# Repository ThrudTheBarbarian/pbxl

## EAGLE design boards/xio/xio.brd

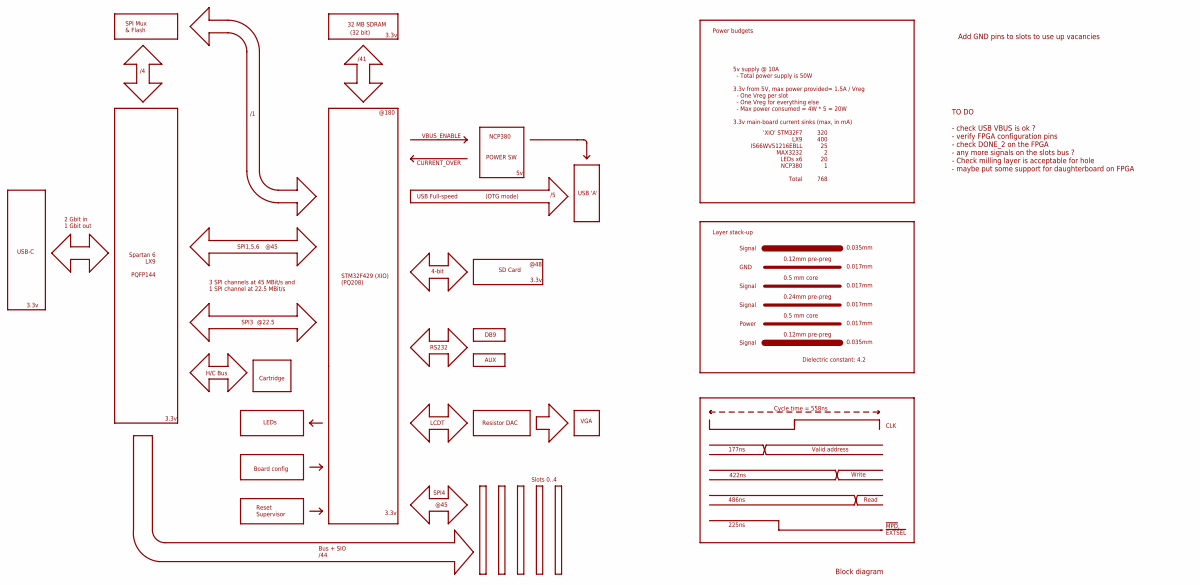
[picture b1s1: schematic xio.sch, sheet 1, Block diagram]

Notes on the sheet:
USB-C
3.3v
STM32F429 (XIO) (PQ208)
SPI4
@45
Slots 0..4
Bus + SIO /44
RS232
32 MB SDRAM
/41
(32 bit)
POWER SW
USB Full-speed
CURRENT_OVER
VBUS_ENABLE
SD Card
@48
@180
NCP380
(OTG mode)
USB 'A'
DB9
5v supply @ 10A - Total power supply is 50W 3.3v from 5V, max power provided= 1.5A / Vreg - One Vreg per slot - One Vreg for everything else - Max power consumed = 4W * 5 = 20W 3.3v main-board current sinks (max, in mA)
'XIO' STM32F7 LX9 IS66WV51216EBLL MAX3232 LEDs x6 NCP380 Total
320 400 25 2 20 1 768
0.5 mm core
0.12mm pre-preg
0.035mm
0.017mm
Layer stack-up
GND
Power
Dielectric constant: 4.2
Cycle time = 558ns
Valid address
Write
Read
177ns
422ns
486ns

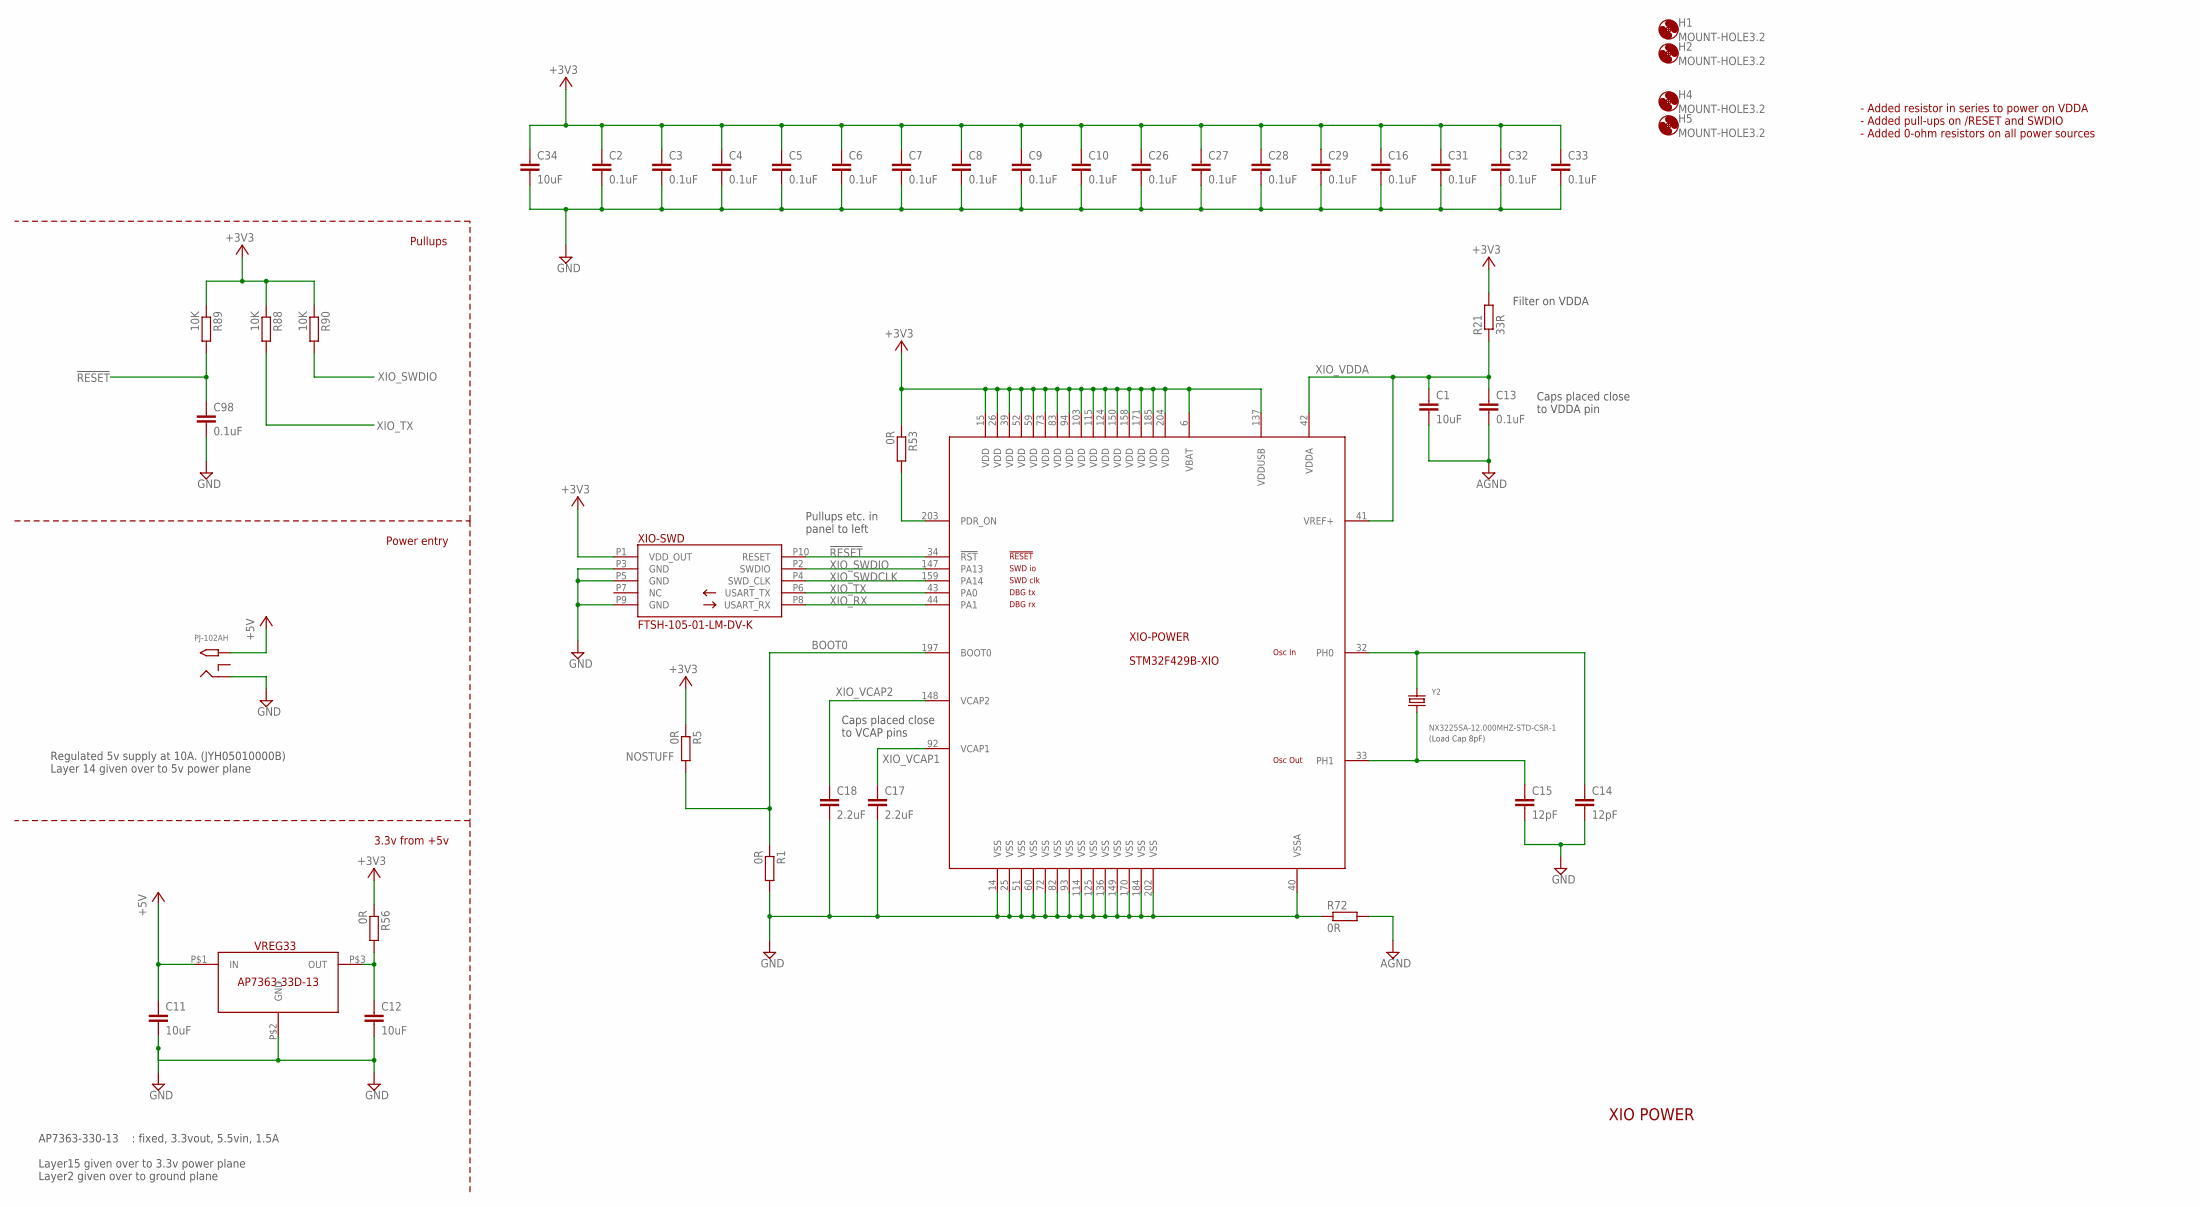
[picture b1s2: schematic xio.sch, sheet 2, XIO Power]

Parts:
C1, C11, C12, C34: 10uF; C0402K
C2, C3, C4, C5, C6, C7, C8, C9, C10, C13, C16, C26, C27, C28, C29, C31, C32, C33, C98: 0.1uF; C0402K
C14, C15: 12pF; C0402K
C17, C18: 2.2uF; C0402K
H1, H2, H4, H5: MOUNT-HOLE3.2; 3,2
PJ-102AH: PJ-102AH; PJ-102A
R1, R5, R53, R56, R72: 0R; R0402
R21: 33R; R0402
R88, R89, R90: 10K; R0402
VREG33: AP7363-33D-13; TO252-3L
XIO: STM32F429B-XIO; PQFP208
XIO-SWD: FTSH-105-01-LM-DV-K; SWD_DEBUG
Y2: NX3225SA-12.000MHZ-STD-CSR-1; CRYSTAL_3.2X2.5

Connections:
!RESET!: C98.1, R89.2, XIO.34 (!RST!), XIO-SWD.P10 (RESET); also elsewhere on the board
+3V3: C2.1, C3.1, C4.1, C5.1, C6.1, C7.1, C8.1, C9.1, C10.1, C16.1, C26.1, C27.1, C28.1, C29.1, C31.1, C32.1, C33.1, C34.1, R5.1, R21.2, R53.1, R56.1, R88.1, R89.1, R90.1, XIO.6 (VBAT), XIO.15 (VDD), XIO.26 (VDD), XIO.39 (VDD), XIO.52 (VDD), XIO.59 (VDD), XIO.73 (VDD), XIO.83 (VDD), XIO.94 (VDD), XIO.103 (VDD), XIO.115 (VDD), XIO.124 (VDD), XIO.137 (VDDUSB), XIO.150 (VDD), XIO.158 (VDD), XIO.171 (VDD), XIO.185 (VDD), XIO.204 (VDD), XIO-SWD.P1 (VDD_OUT); also elsewhere on the board
+5V: C11.1, PJ-102AH.TIP, VREG33.P$1 (IN); also elsewhere on the board
AGND: C1.2, C13.2, R72.2
BOOT0: R1.1, R5.2, XIO.197 (BOOT0)
GND: C2.2, C3.2, C4.2, C5.2, C6.2, C7.2, C8.2, C9.2, C10.2, C11.2, C12.2, C14.2, C15.2, C16.2, C17.2, C18.2, C26.2, C27.2, C28.2, C29.2, C31.2, C32.2, C33.2, C34.2, C98.2, PJ-102AH.RING, R1.2, R72.1, VREG33.P$2 (GND), XIO.14 (VSS), XIO.25 (VSS), XIO.40 (VSSA), XIO.51 (VSS), XIO.60 (VSS), XIO.72 (VSS), XIO.82 (VSS), XIO.93 (VSS), XIO.114 (VSS), XIO.125 (VSS), XIO.136 (VSS), XIO.149 (VSS), XIO.170 (VSS), XIO.184 (VSS), XIO.202 (VSS), XIO-SWD.P3 (GND), XIO-SWD.P5 (GND), XIO-SWD.P9 (GND); also elsewhere on the board
unnamed: C15.1, XIO.33 (PH1), Y2.1
unnamed: C14.1, XIO.32 (PH0), Y2.2
unnamed: C12.1, R56.2, VREG33.P$3 (OUT)
PDR_ON: R53.2, XIO.203 (PDR_ON)
XIO_RX: XIO.44 (PA1), XIO-SWD.P8 (USART_RX)
XIO_SWDCLK: XIO.159 (PA14), XIO-SWD.P4 (SWD_CLK)
XIO_SWDIO: R90.2, XIO.147 (PA13), XIO-SWD.P2 (SWDIO)
XIO_TX: R88.2, XIO.43 (PA0), XIO-SWD.P6 (USART_TX)
XIO_VCAP1: C17.1, XIO.92 (VCAP1)
XIO_VCAP2: C18.1, XIO.148 (VCAP2)
XIO_VDDA: C1.1, C13.1, R21.1, XIO.41 (VREF+), XIO.42 (VDDA)

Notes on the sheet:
Power entry
3.3v from +5v
XIO POWER
AP7363-330-13 : fixed, 3.3vout, 5.5vin, 1.5A Layer15 given over to 3.3v power plane Layer2 given over to ground plane
Regulated 5v supply at 10A. (JYH05010000B) Layer 14 given over to 5v power plane
Caps placed close to VDDA pin
Caps placed close to VCAP pins
(Load Cap 8pF)
Pullups
- Added resistor in series to power on VDDA - Added pull-ups on /RESET and SWDIO - Added 0-ohm resistors on all power sources
Filter on VDDA
Pullups etc. in panel to left

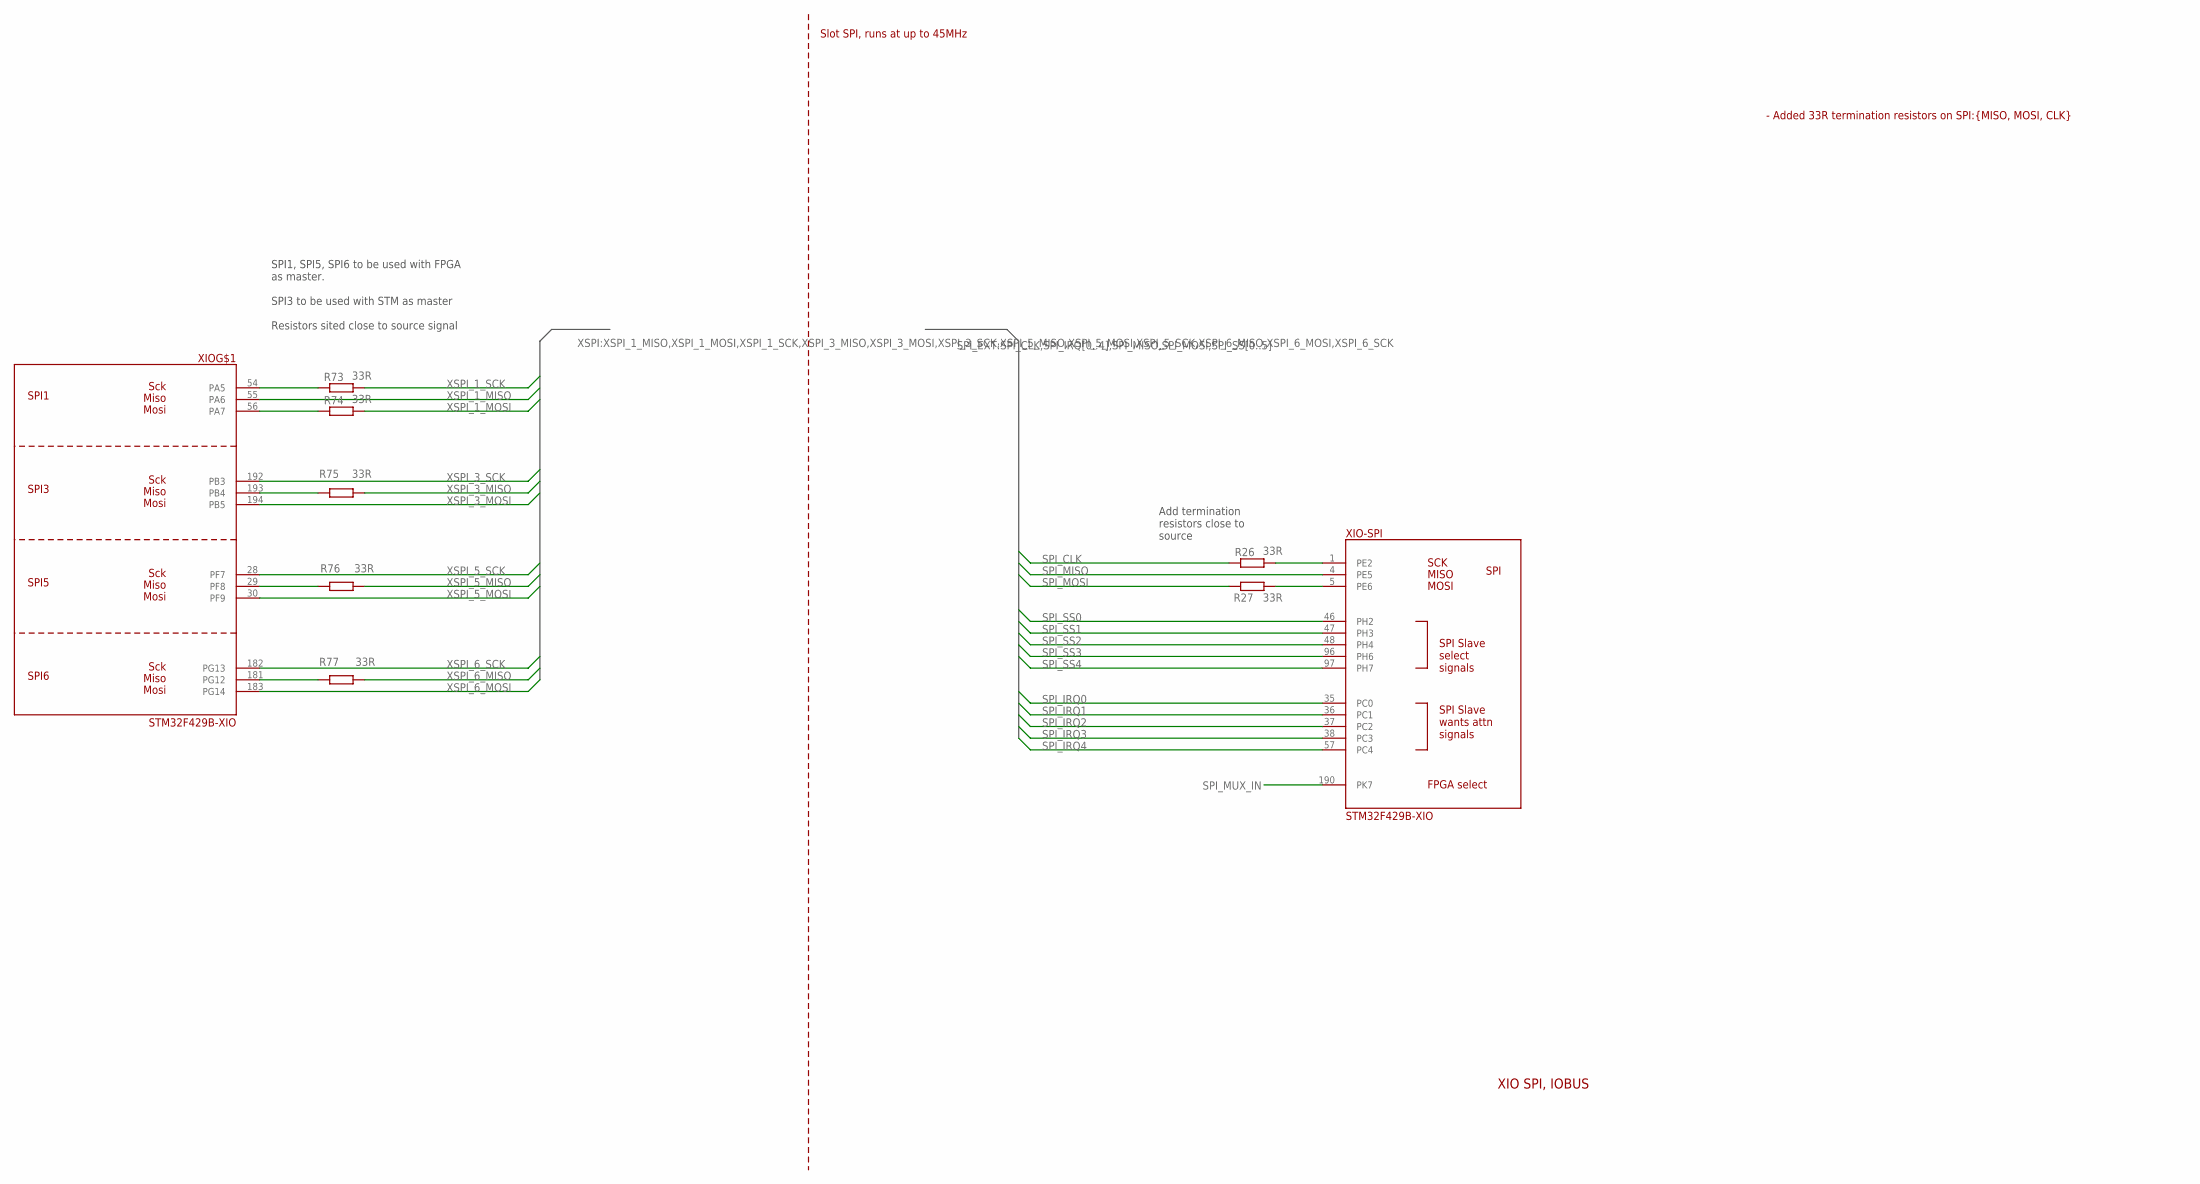
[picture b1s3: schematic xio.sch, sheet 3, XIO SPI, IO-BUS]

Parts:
R26, R27, R73, R74, R75, R76, R77: 33R; R0402
XIO: STM32F429B-XIO; PQFP208

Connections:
unnamed: R26.2, XIO.1 (PE2)
unnamed: R27.2, XIO.5 (PE6)
unnamed: R75.1, XIO.193 (PB4)
unnamed: R76.1, XIO.29 (PF8)
unnamed: R77.1, XIO.181 (PG12)
unnamed: R73.1, XIO.54 (PA5)
unnamed: R74.1, XIO.56 (PA7)
SPI_CLK: R26.1; also elsewhere on the board
SPI_IRQ0: XIO.35 (PC0); also elsewhere on the board
SPI_IRQ1: XIO.36 (PC1); also elsewhere on the board
SPI_IRQ2: XIO.37 (PC2); also elsewhere on the board
SPI_IRQ3: XIO.38 (PC3); also elsewhere on the board
SPI_IRQ4: XIO.57 (PC4); also elsewhere on the board
SPI_MISO: XIO.4 (PE5); also elsewhere on the board
SPI_MOSI: R27.1; also elsewhere on the board
SPI_MUX_IN: XIO.190 (PK7); also elsewhere on the board
SPI_SS0: XIO.46 (PH2); also elsewhere on the board
SPI_SS1: XIO.47 (PH3); also elsewhere on the board
SPI_SS2: XIO.48 (PH4); also elsewhere on the board
SPI_SS3: XIO.96 (PH6); also elsewhere on the board
SPI_SS4: XIO.97 (PH7); also elsewhere on the board
XSPI_1_MISO: XIO.55 (PA6); also elsewhere on the board
XSPI_1_MOSI: R74.2; also elsewhere on the board
XSPI_1_SCK: R73.2; also elsewhere on the board
XSPI_3_MISO: R75.2; also elsewhere on the board
XSPI_3_MOSI: XIO.194 (PB5); also elsewhere on the board
XSPI_3_SCK: XIO.192 (PB3); also elsewhere on the board
XSPI_5_MISO: R76.2; also elsewhere on the board
XSPI_5_MOSI: XIO.30 (PF9); also elsewhere on the board
XSPI_5_SCK: XIO.28 (PF7); also elsewhere on the board
XSPI_6_MISO: R77.2; also elsewhere on the board
XSPI_6_MOSI: XIO.183 (PG14); also elsewhere on the board
XSPI_6_SCK: XIO.182 (PG13); also elsewhere on the board

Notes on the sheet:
Slot SPI, runs at up to 45MHz
XIO SPI, IOBUS
Add termination resistors close to source
- Added 33R termination resistors on SPI:{MISO, MOSI, CLK}
SPI1, SPI5, SPI6 to be used with FPGA as master. SPI3 to be used with STM as master Resistors sited close to source signal

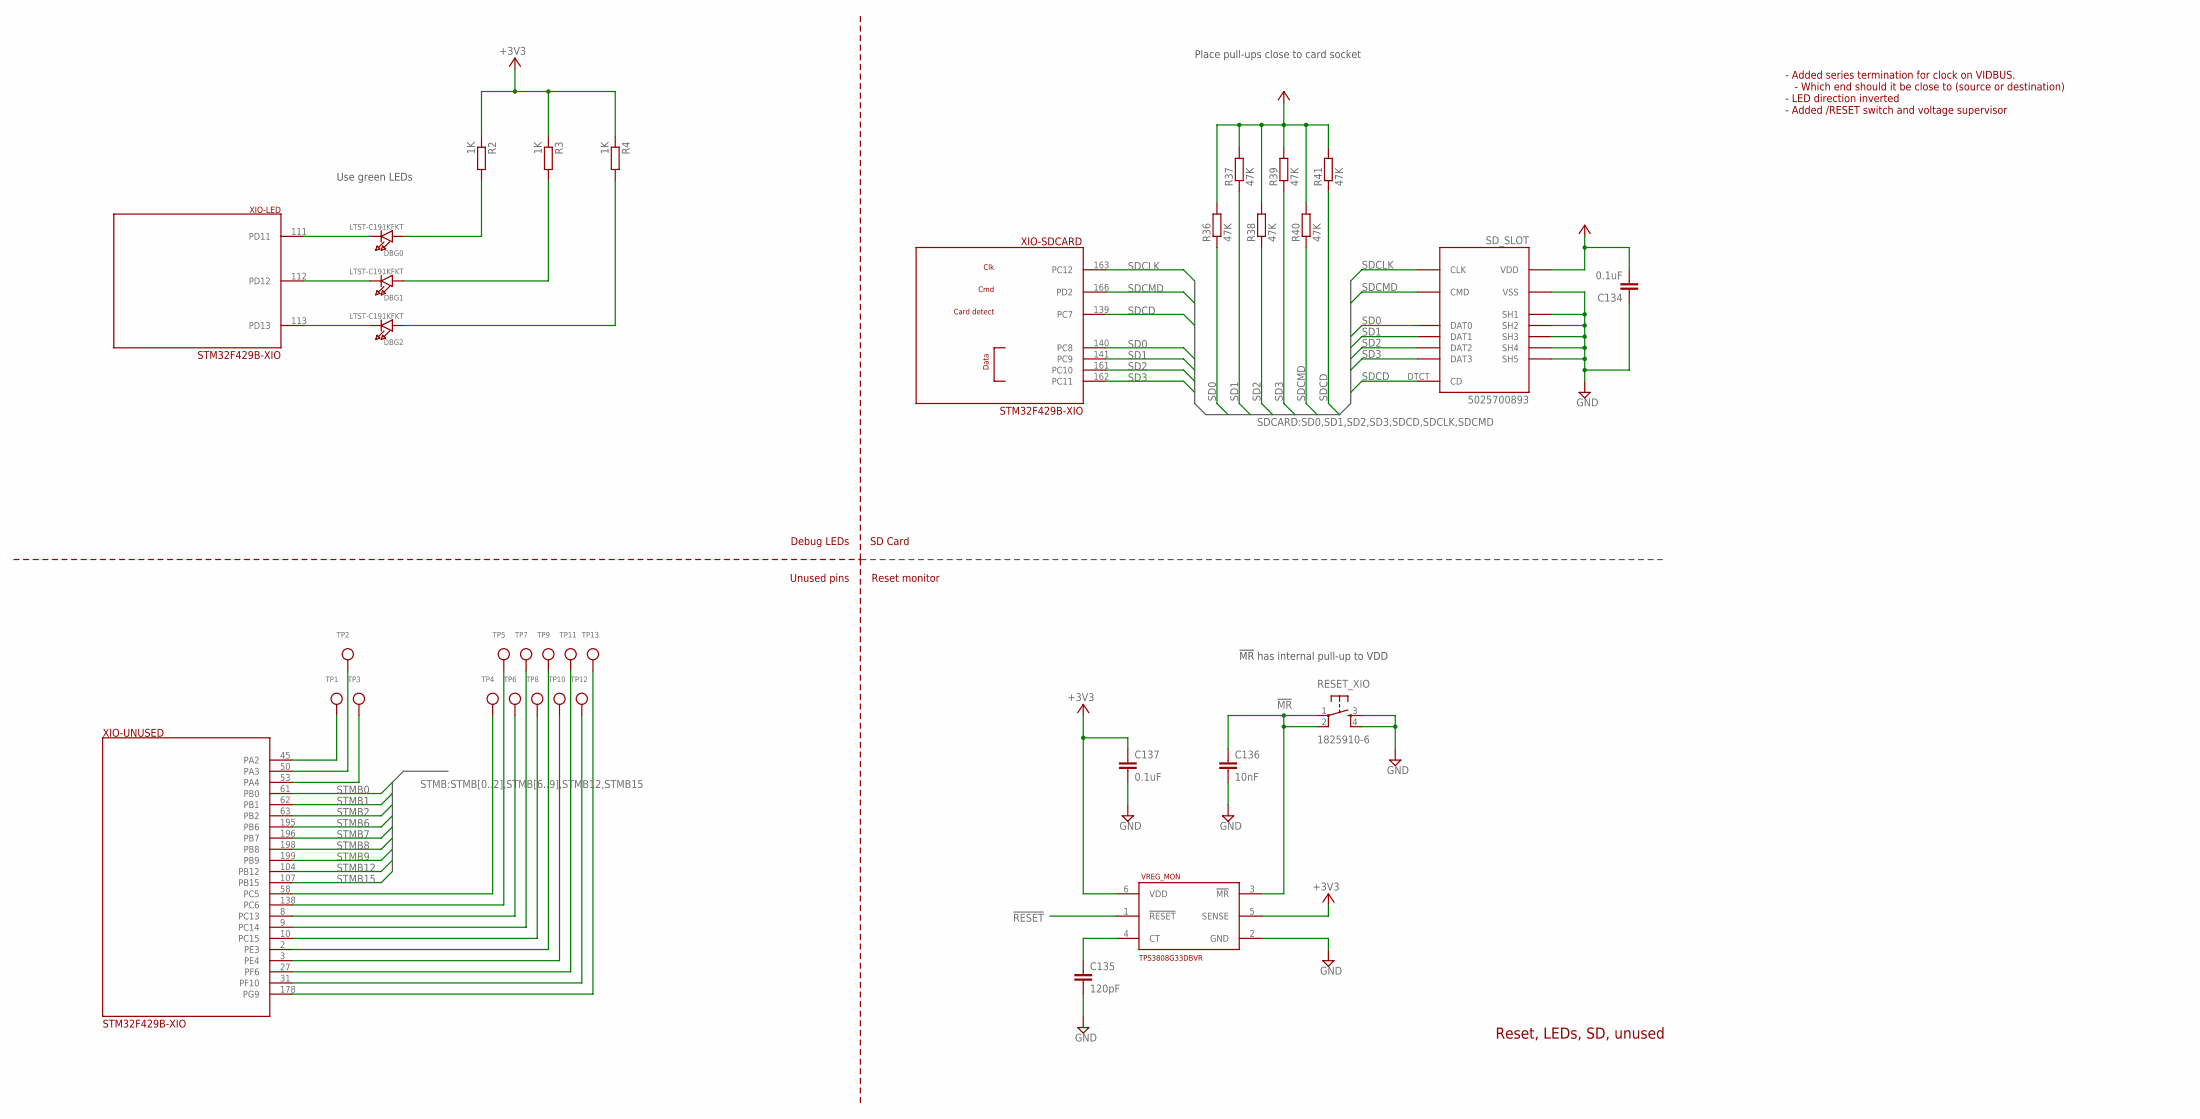
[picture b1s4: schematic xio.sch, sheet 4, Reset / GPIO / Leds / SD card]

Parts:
C134, C137: 0.1uF; C0402K
C135: 120pF; C0402K
C136: 10nF; C0402K
DBG0, DBG1, DBG2: LTST-C191KFKT; CHIPLED_0603
R2, R3, R4: 1K; R0402
R36, R37, R38, R39, R40, R41: 47K; R0402
RESET_XIO: 1825910-6; TACTILE-PTH
SD_SLOT: 5025700893
TP1, TP2, TP3, TP4, TP5, TP6, TP7, TP8, TP9, TP10, TP11, TP12, TP13: TESTPOINTROUND0.5MM; TESTPOINT_ROUND_0.5MM
VREG_MON: TPS3808G33DBVR; SOT23-6
XIO: STM32F429B-XIO; PQFP208

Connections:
!MR!: C136.1, RESET_XIO.1, RESET_XIO.2, VREG_MON.3 (!MR!)
!RESET!: VREG_MON.1 (!RESET!); also elsewhere on the board
+3V3: C134.2, C137.1, R2.1, R3.1, R4.1, R36.2, R37.2, R38.2, R39.2, R40.2, R41.2, SD_SLOT.P$4 (VDD), VREG_MON.5 (SENSE), VREG_MON.6 (VDD); also elsewhere on the board
GND: C134.1, C135.2, C136.2, C137.2, RESET_XIO.3, RESET_XIO.4, SD_SLOT.GND0 (SH1), SD_SLOT.GND1 (SH2), SD_SLOT.GND2 (SH3), SD_SLOT.GND3 (SH4), SD_SLOT.GND4 (SH5), SD_SLOT.P$6 (VSS), VREG_MON.2 (GND); also elsewhere on the board
unnamed: DBG0.A, R2.2
unnamed: DBG0.C, XIO.111 (PD11)
unnamed: DBG1.C, XIO.112 (PD12)
unnamed: DBG2.C, XIO.113 (PD13)
unnamed: DBG1.A, R3.2
unnamed: DBG2.A, R4.2
unnamed: C135.1, VREG_MON.4 (CT)
unnamed: TP1.P$1, XIO.45 (PA2)
unnamed: TP2.P$1, XIO.50 (PA3)
unnamed: TP3.P$1, XIO.53 (PA4)
unnamed: TP4.P$1, XIO.58 (PC5)
unnamed: TP5.P$1, XIO.138 (PC6)
unnamed: TP6.P$1, XIO.8 (PC13)
unnamed: TP7.P$1, XIO.9 (PC14)
unnamed: TP8.P$1, XIO.10 (PC15)
unnamed: TP9.P$1, XIO.2 (PE3)
unnamed: TP10.P$1, XIO.3 (PE4)
unnamed: TP11.P$1, XIO.27 (PF6)
unnamed: TP12.P$1, XIO.31 (PF10)
unnamed: TP13.P$1, XIO.178 (PG9)
SD0: R36.1, SD_SLOT.P$7 (DAT0), XIO.140 (PC8)
SD1: R37.1, SD_SLOT.P$8 (DAT1), XIO.141 (PC9)
SD2: R38.1, SD_SLOT.P$1 (DAT2), XIO.161 (PC10)
SD3: R39.1, SD_SLOT.P$2 (DAT3), XIO.162 (PC11)
SDCD: R41.1, SD_SLOT.DTCT (CD), XIO.139 (PC7)
SDCLK: SD_SLOT.P$5 (CLK), XIO.163 (PC12)
SDCMD: R40.1, SD_SLOT.P$3 (CMD), XIO.166 (PD2)
STMB0: XIO.61 (PB0); also elsewhere on the board
STMB1: XIO.62 (PB1); also elsewhere on the board
STMB2: XIO.63 (PB2); also elsewhere on the board
STMB6: XIO.195 (PB6); also elsewhere on the board
STMB7: XIO.196 (PB7); also elsewhere on the board
STMB8: XIO.198 (PB8); also elsewhere on the board
STMB9: XIO.199 (PB9); also elsewhere on the board
STMB12: XIO.104 (PB12); also elsewhere on the board
STMB15: XIO.107 (PB15); also elsewhere on the board

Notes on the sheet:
Debug LEDs
Unused pins
Reset, LEDs, SD, unused
Use green LEDs
Reset monitor
!MR! has internal pull-up to VDD
- Added series termination for clock on VIDBUS. - Which end should it be close to (source or destination) - LED direction inverted - Added /RESET switch and voltage supervisor
SD Card
Place pull-ups close to card socket

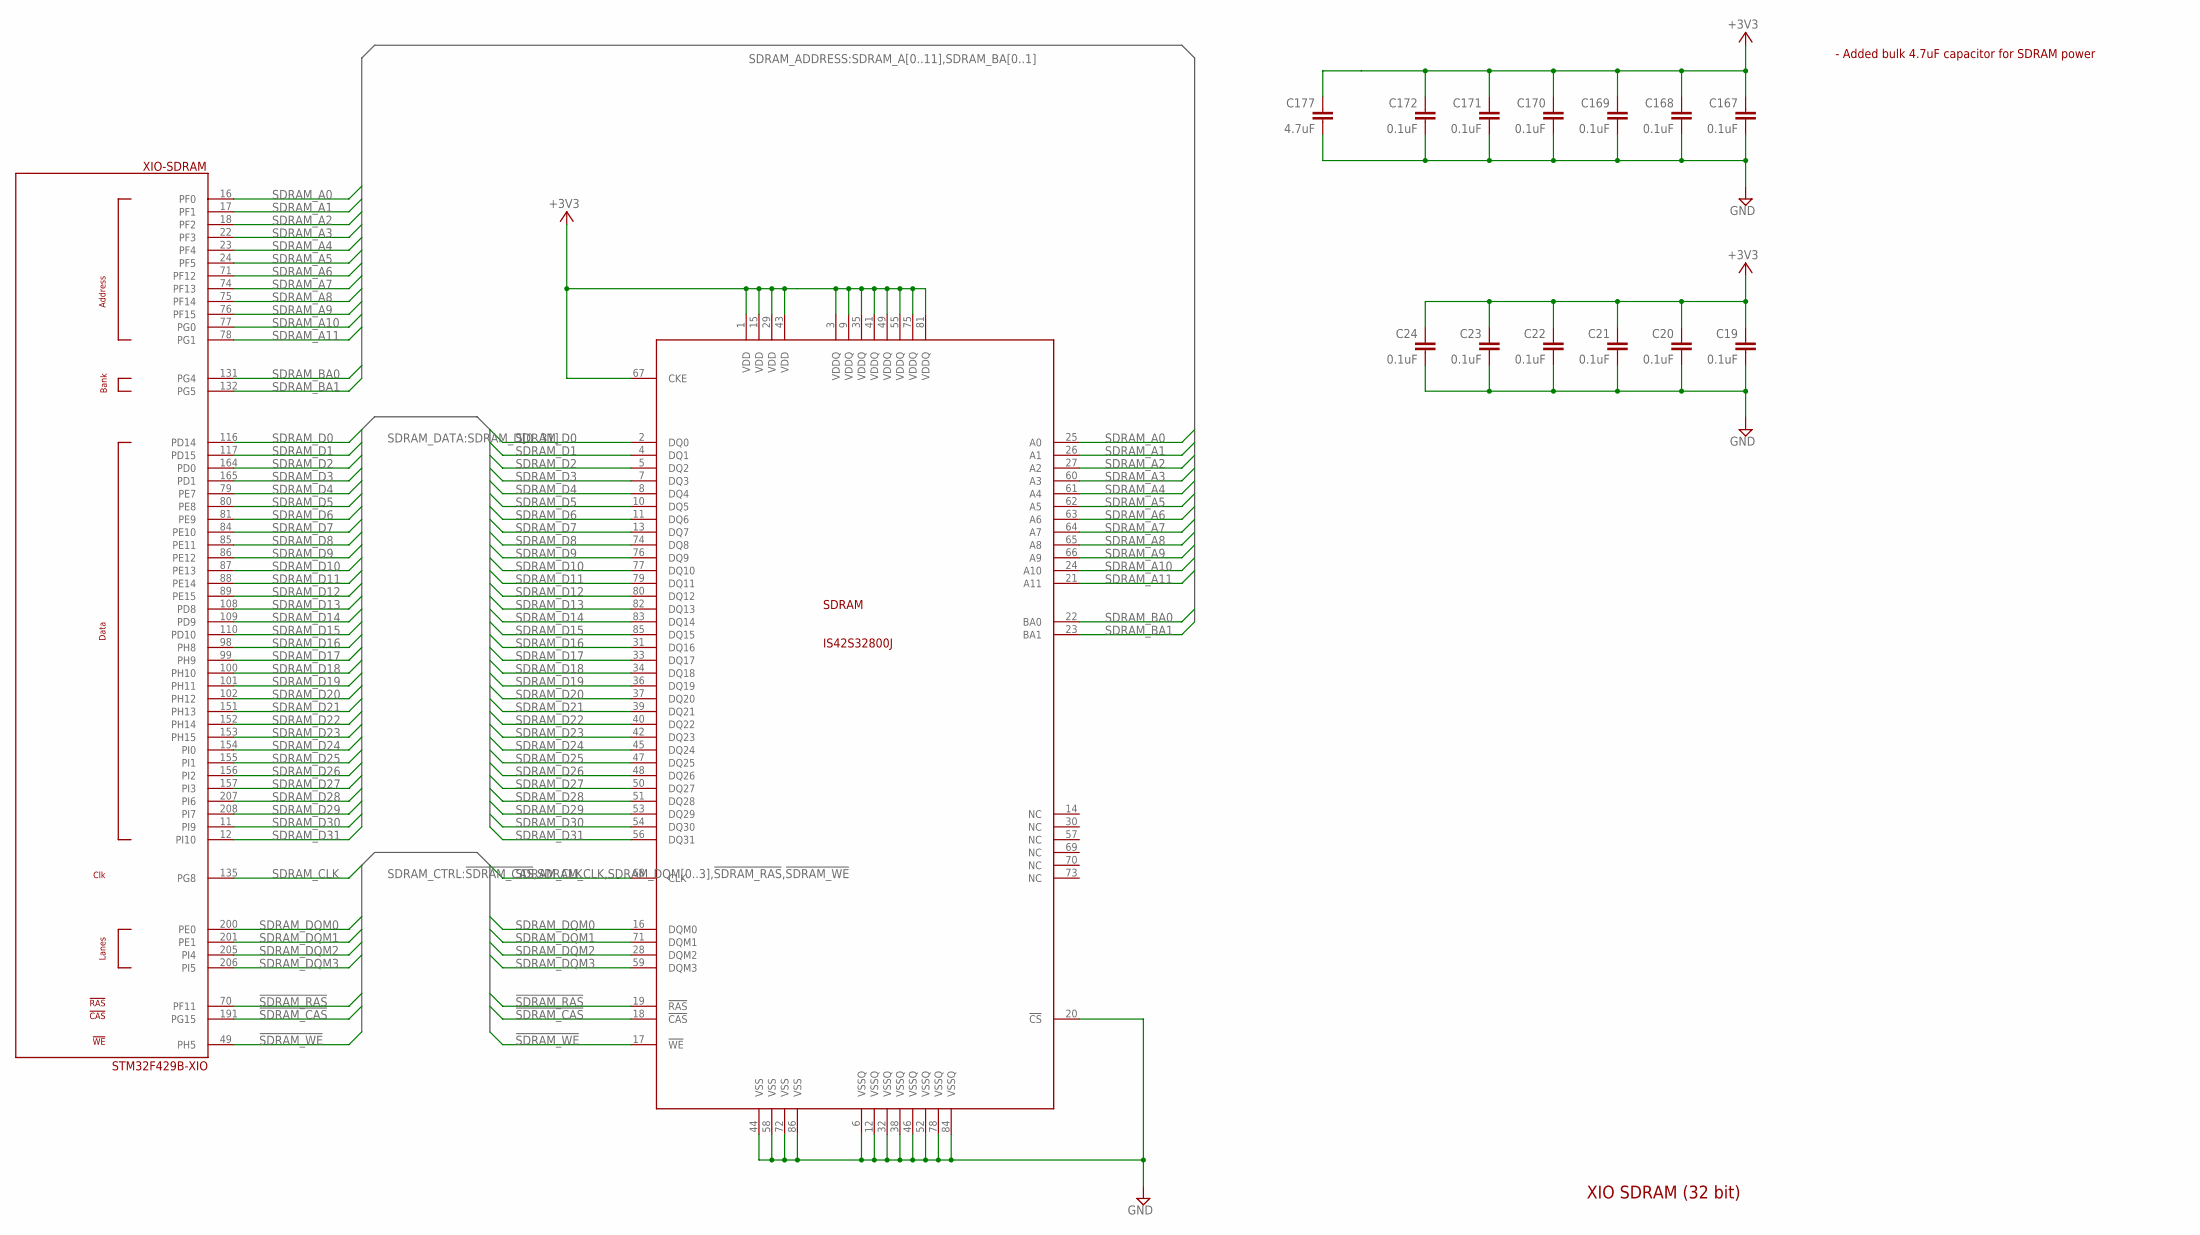
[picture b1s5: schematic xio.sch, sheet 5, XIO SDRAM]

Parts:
C19, C20, C21, C22, C23, C24, C167, C168, C169, C170, C171, C172: 0.1uF; C0402K
C177: 4.7uF; C0402K
SDRAM: IS42S32800J; SOP50P1176X120-86
XIO: STM32F429B-XIO; PQFP208

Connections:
!SDRAM_CAS!: SDRAM.18 (!CAS!), XIO.191 (PG15)
!SDRAM_RAS!: SDRAM.19 (!RAS!), XIO.70 (PF11)
!SDRAM_WE!: SDRAM.17 (!WE!), XIO.49 (PH5)
+3V3: C19.1, C20.1, C21.1, C22.1, C23.1, C24.1, C167.1, C168.1, C169.1, C170.1, C171.1, C172.1, C177.1, SDRAM.1 (VDD), SDRAM.3 (VDDQ), SDRAM.9 (VDDQ), SDRAM.15 (VDD), SDRAM.29 (VDD), SDRAM.35 (VDDQ), SDRAM.41 (VDDQ), SDRAM.43 (VDD), SDRAM.49 (VDDQ), SDRAM.55 (VDDQ), SDRAM.67 (CKE), SDRAM.75 (VDDQ), SDRAM.81 (VDDQ); also elsewhere on the board
GND: C19.2, C20.2, C21.2, C22.2, C23.2, C24.2, C167.2, C168.2, C169.2, C170.2, C171.2, C172.2, C177.2, SDRAM.6 (VSSQ), SDRAM.12 (VSSQ), SDRAM.20 (!CS!), SDRAM.32 (VSSQ), SDRAM.38 (VSSQ), SDRAM.44 (VSS), SDRAM.46 (VSSQ), SDRAM.52 (VSSQ), SDRAM.58 (VSS), SDRAM.72 (VSS), SDRAM.78 (VSSQ), SDRAM.84 (VSSQ), SDRAM.86 (VSS); also elsewhere on the board
SDRAM_A0: SDRAM.25 (A0), XIO.16 (PF0)
SDRAM_A1: SDRAM.26 (A1), XIO.17 (PF1)
SDRAM_A2: SDRAM.27 (A2), XIO.18 (PF2)
SDRAM_A3: SDRAM.60 (A3), XIO.22 (PF3)
SDRAM_A4: SDRAM.61 (A4), XIO.23 (PF4)
SDRAM_A5: SDRAM.62 (A5), XIO.24 (PF5)
SDRAM_A6: SDRAM.63 (A6), XIO.71 (PF12)
SDRAM_A7: SDRAM.64 (A7), XIO.74 (PF13)
SDRAM_A8: SDRAM.65 (A8), XIO.75 (PF14)
SDRAM_A9: SDRAM.66 (A9), XIO.76 (PF15)
SDRAM_A10: SDRAM.24 (A10), XIO.77 (PG0)
SDRAM_A11: SDRAM.21 (A11), XIO.78 (PG1)
SDRAM_BA0: SDRAM.22 (BA0), XIO.131 (PG4)
SDRAM_BA1: SDRAM.23 (BA1), XIO.132 (PG5)
SDRAM_CLK: SDRAM.68 (CLK), XIO.135 (PG8)
SDRAM_D0: SDRAM.2 (DQ0), XIO.116 (PD14)
SDRAM_D1: SDRAM.4 (DQ1), XIO.117 (PD15)
SDRAM_D2: SDRAM.5 (DQ2), XIO.164 (PD0)
SDRAM_D3: SDRAM.7 (DQ3), XIO.165 (PD1)
SDRAM_D4: SDRAM.8 (DQ4), XIO.79 (PE7)
SDRAM_D5: SDRAM.10 (DQ5), XIO.80 (PE8)
SDRAM_D6: SDRAM.11 (DQ6), XIO.81 (PE9)
SDRAM_D7: SDRAM.13 (DQ7), XIO.84 (PE10)
SDRAM_D8: SDRAM.74 (DQ8), XIO.85 (PE11)
SDRAM_D9: SDRAM.76 (DQ9), XIO.86 (PE12)
SDRAM_D10: SDRAM.77 (DQ10), XIO.87 (PE13)
SDRAM_D11: SDRAM.79 (DQ11), XIO.88 (PE14)
SDRAM_D12: SDRAM.80 (DQ12), XIO.89 (PE15)
SDRAM_D13: SDRAM.82 (DQ13), XIO.108 (PD8)
SDRAM_D14: SDRAM.83 (DQ14), XIO.109 (PD9)
SDRAM_D15: SDRAM.85 (DQ15), XIO.110 (PD10)
SDRAM_D16: SDRAM.31 (DQ16), XIO.98 (PH8)
SDRAM_D17: SDRAM.33 (DQ17), XIO.99 (PH9)
SDRAM_D18: SDRAM.34 (DQ18), XIO.100 (PH10)
SDRAM_D19: SDRAM.36 (DQ19), XIO.101 (PH11)
SDRAM_D20: SDRAM.37 (DQ20), XIO.102 (PH12)
SDRAM_D21: SDRAM.39 (DQ21), XIO.151 (PH13)
SDRAM_D22: SDRAM.40 (DQ22), XIO.152 (PH14)
SDRAM_D23: SDRAM.42 (DQ23), XIO.153 (PH15)
SDRAM_D24: SDRAM.45 (DQ24), XIO.154 (PI0)
SDRAM_D25: SDRAM.47 (DQ25), XIO.155 (PI1)
SDRAM_D26: SDRAM.48 (DQ26), XIO.156 (PI2)
SDRAM_D27: SDRAM.50 (DQ27), XIO.157 (PI3)
SDRAM_D28: SDRAM.51 (DQ28), XIO.207 (PI6)
SDRAM_D29: SDRAM.53 (DQ29), XIO.208 (PI7)
SDRAM_D30: SDRAM.54 (DQ30), XIO.11 (PI9)
SDRAM_D31: SDRAM.56 (DQ31), XIO.12 (PI10)
SDRAM_DQM0: SDRAM.16 (DQM0), XIO.200 (PE0)
SDRAM_DQM1: SDRAM.71 (DQM1), XIO.201 (PE1)
SDRAM_DQM2: SDRAM.28 (DQM2), XIO.205 (PI4)
SDRAM_DQM3: SDRAM.59 (DQM3), XIO.206 (PI5)

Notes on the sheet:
- Added bulk 4.7uF capacitor for SDRAM power
XIO SDRAM (32 bit)

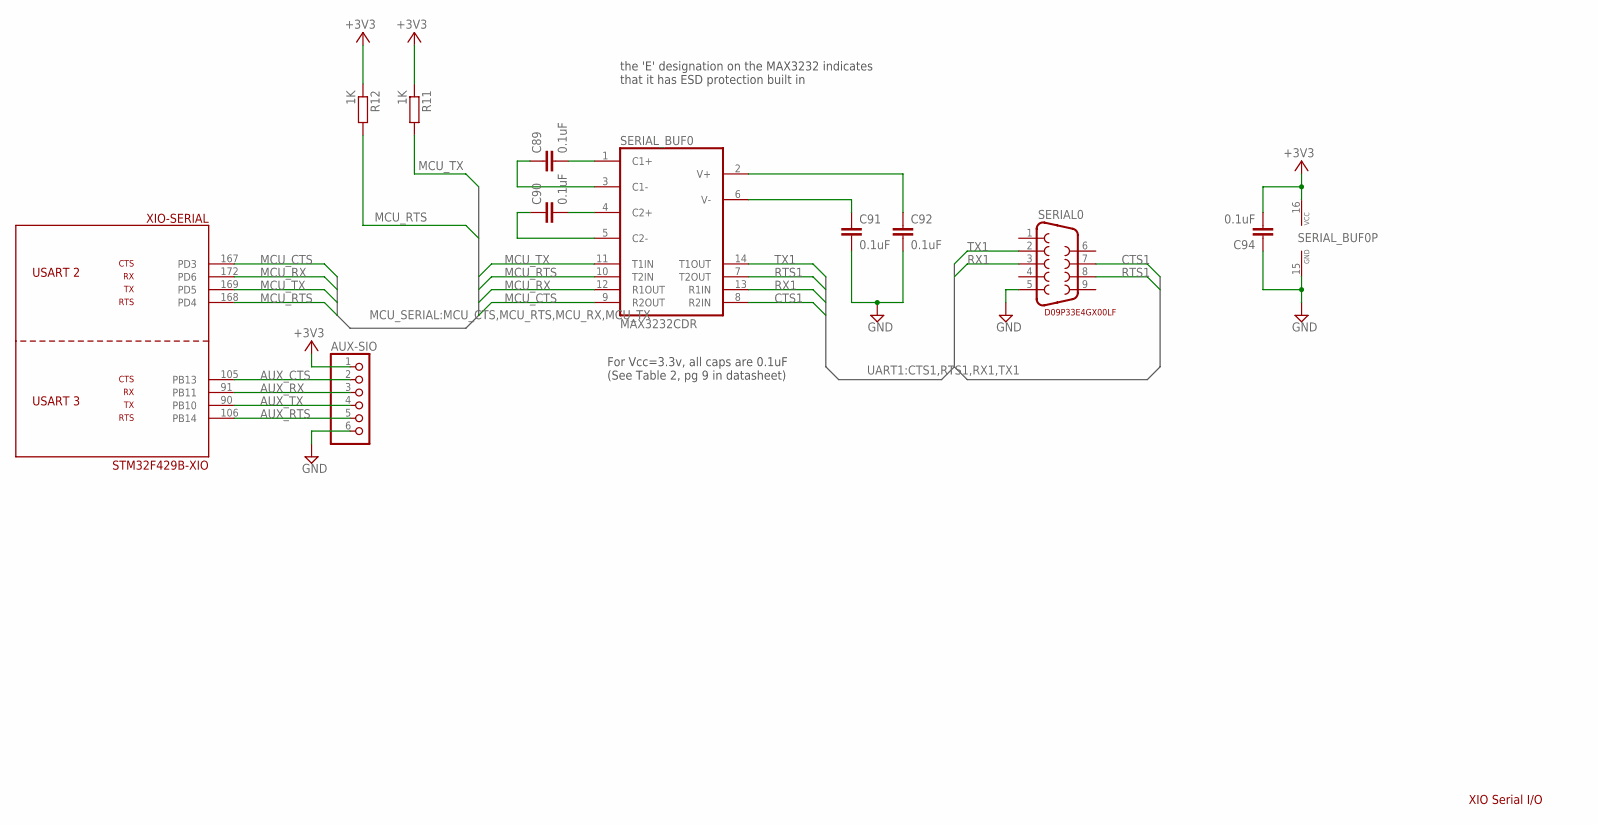
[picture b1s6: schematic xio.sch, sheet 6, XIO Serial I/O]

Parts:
AUX-SIO: PINHD-1X6; 1X06
C89, C90, C91, C92, C94: 0.1uF; C0402K
R11, R12: 1K; R0402
SERIAL0: DB9
SERIAL_BUF0: MAX3232CDR; SO16
XIO: STM32F429B-XIO; PQFP208

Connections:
+3V3: AUX-SIO.1, C94.2, R11.1, R12.1, SERIAL_BUF0.16 (VCC); also elsewhere on the board
AUX_CTS: AUX-SIO.2, XIO.105 (PB13)
AUX_RTS: AUX-SIO.5, XIO.106 (PB14)
AUX_RX: AUX-SIO.3, XIO.91 (PB11)
AUX_TX: AUX-SIO.4, XIO.90 (PB10)
CTS1: SERIAL0.7, SERIAL_BUF0.8 (R2IN)
GND: AUX-SIO.6, C91.2, C92.2, C94.1, SERIAL0.5, SERIAL_BUF0.15 (GND); also elsewhere on the board
MCU_CTS: SERIAL_BUF0.9 (R2OUT), XIO.167 (PD3)
MCU_RTS: R12.2, SERIAL_BUF0.10 (T2IN), XIO.168 (PD4)
MCU_RX: SERIAL_BUF0.12 (R1OUT), XIO.172 (PD6)
MCU_TX: R11.2, SERIAL_BUF0.11 (T1IN), XIO.169 (PD5)
unnamed: C89.2, SERIAL_BUF0.1 (C1+)
unnamed: C89.1, SERIAL_BUF0.3 (C1-)
unnamed: C90.2, SERIAL_BUF0.4 (C2+)
unnamed: C90.1, SERIAL_BUF0.5 (C2-)
unnamed: C91.1, SERIAL_BUF0.6 (V-)
unnamed: C92.1, SERIAL_BUF0.2 (V+)
RTS1: SERIAL0.8, SERIAL_BUF0.7 (T2OUT)
RX1: SERIAL0.3, SERIAL_BUF0.13 (R1IN)
TX1: SERIAL0.2, SERIAL_BUF0.14 (T1OUT)

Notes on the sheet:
XIO Serial I/O
For Vcc=3.3v, all caps are 0.1uF (See Table 2, pg 9 in datasheet)
the 'E' designation on the MAX3232 indicates that it has ESD protection built in
D09P33E4GX00LF

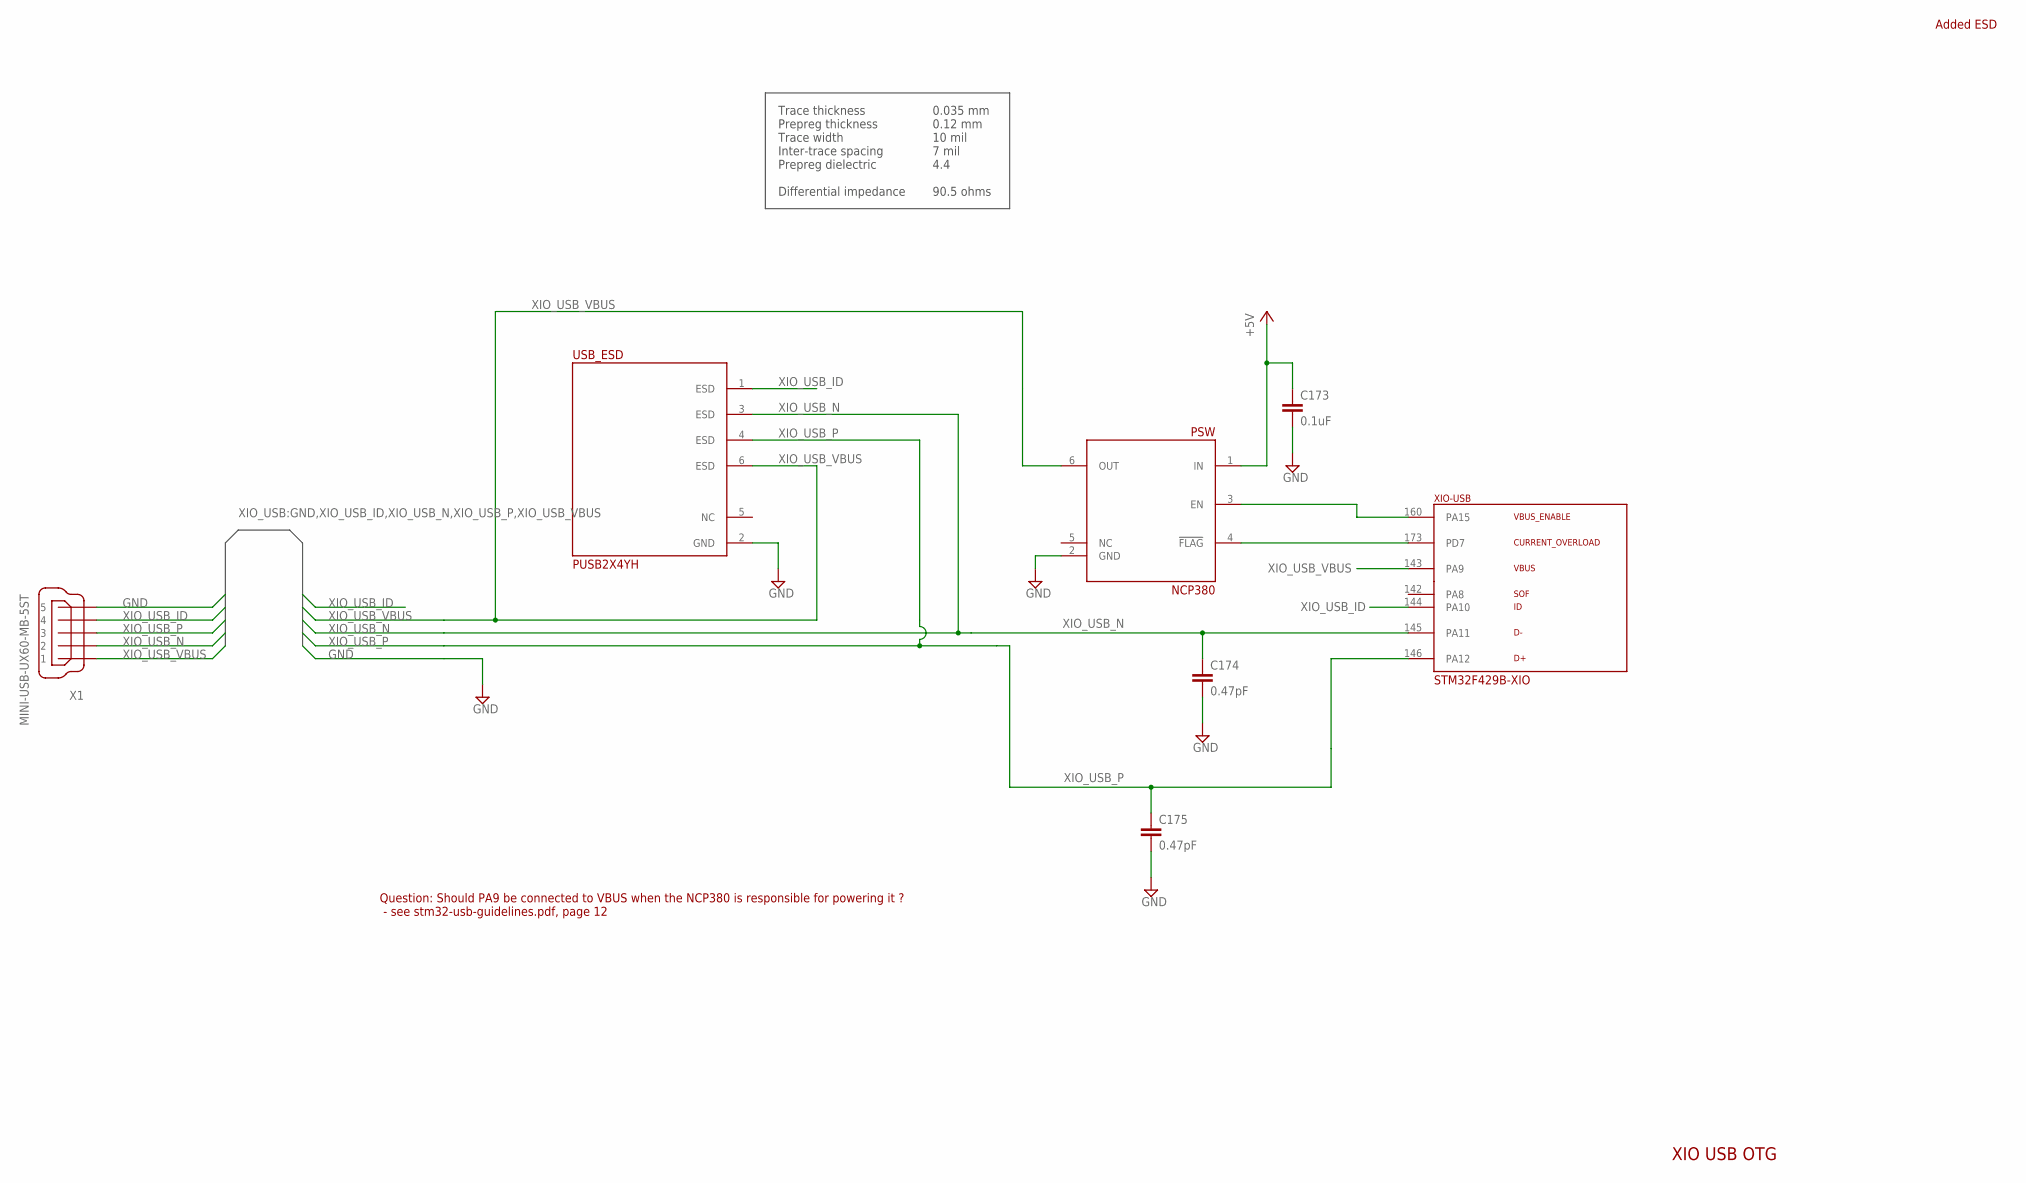
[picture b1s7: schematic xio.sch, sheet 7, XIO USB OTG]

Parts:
C173: 0.1uF; C0402K
C174, C175: 0.47pF; C0402K
PSW: NCP380; SOT23-6
USB_ESD: PUSB2X4YH; SOT363
X1: MINI-USB-UX60-MB-5ST; UX60-MB-5ST
XIO: STM32F429B-XIO; PQFP208

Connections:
+5V: C173.1, PSW.1 (IN); also elsewhere on the board
GND: C173.2, C174.2, C175.2, PSW.2 (GND), USB_ESD.2 (GND), X1.5; also elsewhere on the board
unnamed: PSW.3 (EN), XIO.160 (PA15)
unnamed: PSW.4 (!FLAG!), XIO.173 (PD7)
XIO_USB_ID: USB_ESD.1 (ESD), X1.4, XIO.144 (PA10)
XIO_USB_N: C174.1, USB_ESD.3 (ESD), X1.2, XIO.145 (PA11)
XIO_USB_P: C175.1, USB_ESD.4 (ESD), X1.3, XIO.146 (PA12)
XIO_USB_VBUS: PSW.6 (OUT), USB_ESD.6 (ESD), X1.1, XIO.143 (PA9)

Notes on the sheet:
Trace thickness Prepreg thickness Trace width Inter-trace spacing Prepreg dielectric Differential impedance
0.035 mm 0.12 mm 10 mil 7 mil 4.4 90.5 ohms
Added ESD
XIO USB OTG
Question: Should PA9 be connected to VBUS when the NCP380 is responsible for powering it ? - see stm32-usb-guidelines.pdf, page 12

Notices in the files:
parts and their libraries:
SparkFun: Licensing: CC v3.0 Share-Alike You are welcome to use this library for commercial purposes.
InputOutputIO: Copyright: Würth Elektronik
SparkFun-DiscreteSemi: Licensing: Creative Commons ShareAlike 4.0 International - https://creativecommons.org/licenses/by-sa/4.0
